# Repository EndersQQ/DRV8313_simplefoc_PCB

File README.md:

# DRV8313_simplefoc_PCB
A FOC driver board for controlling multiple BLDC motors using **SimpleFOC** and the **DRV8313** 3‑phase driver.

- Project: **FOC Motor Driver PCB**
- Driver IC: **Texas Instruments DRV8313**
- Firmware ecosystem: **Arduino and SimpleFOC library**

---

## Table of Contents
- [DRV8313_simplefoc_PCB](#drv8313_simplefoc_pcb)
  - [Overview](#overview)
  - [Features](#features)
  - [Repository Structure](#repository-structure)
  - [Hardware (PCB)](#hardware-pcb)
  - [Bill of Materials (BOM)](#bill-of-materials-bom)

---

## Overview
**DRV8313_simplefoc_PCB** is a compact motor driver board intended for **Field Oriented Control (FOC)** of BLDC motors. The board is designed to be used with a microcontroller running **SimpleFOC**, and provides the power stage based on the **DRV8313**.

> Goal: make it easy to build multi-motor setups by repeating the same driver channel design and keeping wiring/bring-up straightforward.

---

## Features
- DRV8313-based **3-phase BLDC** driver stage
- Designed for **SimpleFOC compatibility**
- Multi-motor oriented layout (repeatable channels)
- Test points / headers for bring-up (PWM, enable, faults, power) *(edit to match your PCB)*
- Power input + motor phase outputs *(edit to match your PCB)*

---

## Repository Structure
> Adjust folder names to match your repo.

- `Hardware/` – schematics, PCB layout, fabrication outputs (Gerbers)
- `BOM/` – BOM files, part numbers, assembly notes
- `Docs/` – wiring diagrams, photos, notes

---

## Hardware (PCB)
**Driver:** DRV8313 (3 half-bridges, BLDC driver)

### Key specs (fill these in)
- Supply voltage: **12 V**
- Max phase current (design target): **3 A**
- PWM input: **3 PWM**
- Control interface: **STM32**

### Photos / renders
Add images like this (put your images in `Docs/` or use GitHub uploads):

---

## Bill of Materials (BOM)
List critical parts (example layout below):

1. **DRV8313** – 3-phase driver IC
2. **ASC712** – Hall-effect current sensor
3. **LMR36015S** – synchronous step-down buck converter
4. **Connectors**
   - Power input (VIN/GND)
   - Motor outputs (U/V/W)
   - Control header (PWM/EN/GND/FAULT, etc.)
   - current sense output 

---

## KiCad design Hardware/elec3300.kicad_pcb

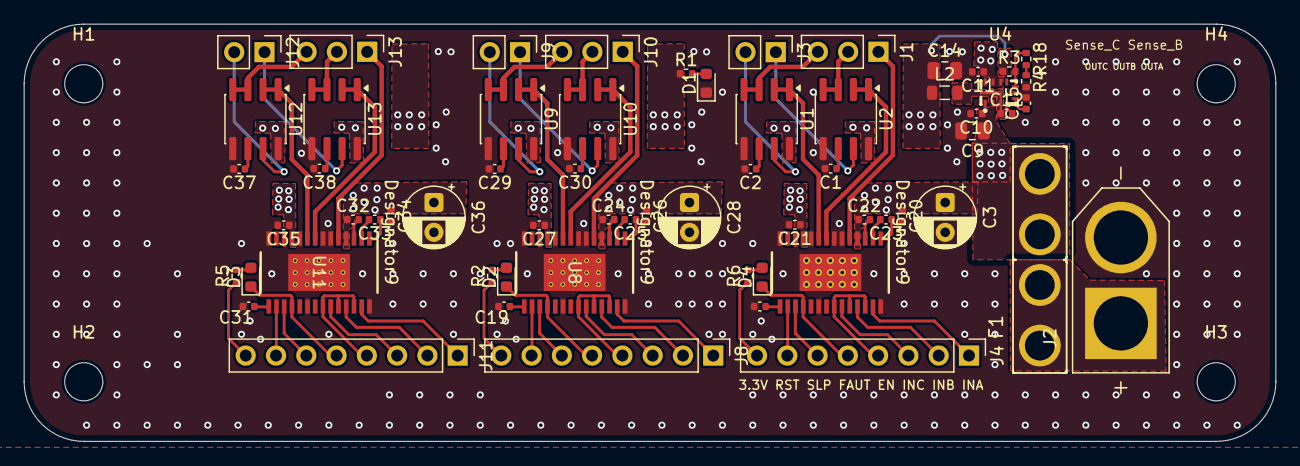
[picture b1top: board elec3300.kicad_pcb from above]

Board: 4 copper layers, 105.0 x 35.0 mm, 67 parts (0 on the bottom side), 74 nets.

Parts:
C1, C2, C29, C30, C37, C38: 1n; C_0402_1005Metric
C3, C28, C36: 100uF; CP_Radial_D5.0mm_P2.50mm
C8, C19, C31: 220n; C_0402_1005Metric
C9: 2.2u; C_0805_2012Metric
C10, C11: 22n; C_0402_1005Metric
C12, C20, C21, C22, C24, C26, C27, C32, C34, C35: 100n; C_0402_1005Metric
C14: 22u; C_0805_2012Metric
C15: 1u; C_0402_1005Metric
C23, C25, C33: 10n; C_0402_1005Metric
D1: LED; LED_0603_1608Metric
D2, D3, D4: LED; D_0603_1608Metric
F1: 01000057Z; FUSE_01000057Z
H1, H2, H3, H4: MountingHole; MountingHole_3.2mm_M3
J1, J10, J13: Conn_01x03; PinHeader_1x03_P2.54mm_Vertical
J2: XT60-M; AMASS_XT60-M
J3, J9, J12: Conn_01x02; PinHeader_1x02_P2.54mm_Vertical
J4, J8, J11: Conn_01x08; PinHeader_1x08_P2.54mm_Vertical
L2: 10u; L_0805_2012Metric
R1: 250; R_0402_1005Metric
R2, R5, R6: 1k5; R_0402_1005Metric
R3: 100k; R_0402_1005Metric
R4: 20k; R_0402_1005Metric
R18: 4.7k; R_0402_1005Metric
U1, U2, U9, U10, U12, U13: ACS712xLCTR-05B; SOIC-8_3.9x4.9mm_P1.27mm
U3, U8, U11: DRV8313PWP; PWP0028F_L
U4: LMR36015SFBRNXR; VQFN-12_L3.0-W2.0-P0.65-BL_TI_RNX

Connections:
+3.3V: J4.8, J8.8, J11.8, R2.1, R5.1, R6.1
+5V: C14.1, L2.1, R1.1, R3.1, U1.8 (VCC), U2.8 (VCC), U9.8 (VCC), U10.8 (VCC), U12.8 (VCC), U13.8 (VCC)
+12V: C3.1, C9.1, C10.1, C11.1, C20.1, C21.1, C22.1, C24.1, C26.1, C27.1, C28.1, C32.1, C34.1, C35.1, C36.1, F1.2A, F1.2B, U3.4 (VM), U3.11 (VM), U4.2 (VIN), U4.9 (EN), U4.10 (VIN), U8.4 (VM), U8.11 (VM), U11.4 (VM), U11.11 (VM)
/DRV8313_1/DRV_EN: J4.4, U3.22 (EN3), U3.24 (EN2), U3.26 (EN1)
/DRV8313_1/DRV_INA: J4.1, U3.27 (IN1)
/DRV8313_1/DRV_INB: J4.2, U3.25 (IN2)
/DRV8313_1/DRV_INC: J4.3, U3.23 (IN3)
/DRV8313_1/ISENSE_B: J3.1, U2.7 (VIOUT)
/DRV8313_1/ISENSE_C: J3.2, U1.7 (VIOUT)
/DRV8313_1/OUTA: J1.1, U3.5 (OUT1)
/DRV8313_1/OUTB: J1.2, U2.3 (IP-), U2.4 (IP-)
/DRV8313_1/OUTC: J1.3, U1.3 (IP-), U1.4 (IP-)
/DRV8313_1/PHB: U2.1 (IP+), U2.2 (IP+), U3.8 (OUT2)
/DRV8313_1/PHC: U1.1 (IP+), U1.2 (IP+), U3.9 (OUT3)
/DRV8313_1/~DRV_NFAULT: D4.1 (K), J4.5, U3.18 (~FAULT)
/DRV8313_1/~DRV_NRST: J4.7, U3.16 (~RESET)
/DRV8313_1/~DRV_NSLEEP: J4.6, U3.17 (~SLEEP)
/DRV8313_3/DRV_EN: J8.4, U8.22 (EN3), U8.24 (EN2), U8.26 (EN1)
/DRV8313_3/DRV_INA: J8.1, U8.27 (IN1)
/DRV8313_3/DRV_INB: J8.2, U8.25 (IN2)
/DRV8313_3/DRV_INC: J8.3, U8.23 (IN3)
/DRV8313_3/ISENSE_B: J9.1, U10.7 (VIOUT)
/DRV8313_3/ISENSE_C: J9.2, U9.7 (VIOUT)
/DRV8313_3/OUTA: J10.1, U8.5 (OUT1)
/DRV8313_3/OUTB: J10.2, U10.3 (IP-), U10.4 (IP-)
/DRV8313_3/OUTC: J10.3, U9.3 (IP-), U9.4 (IP-)
/DRV8313_3/PHB: U8.8 (OUT2), U10.1 (IP+), U10.2 (IP+)
/DRV8313_3/PHC: U8.9 (OUT3), U9.1 (IP+), U9.2 (IP+)
/DRV8313_3/~DRV_NFAULT: D2.1 (K), J8.5, U8.18 (~FAULT)
/DRV8313_3/~DRV_NRST: J8.7, U8.16 (~RESET)
/DRV8313_3/~DRV_NSLEEP: J8.6, U8.17 (~SLEEP)
/DRV8313_4/DRV_EN: J11.4, U11.22 (EN3), U11.24 (EN2), U11.26 (EN1)
/DRV8313_4/DRV_INA: J11.1, U11.27 (IN1)
/DRV8313_4/DRV_INB: J11.2, U11.25 (IN2)
/DRV8313_4/DRV_INC: J11.3, U11.23 (IN3)
/DRV8313_4/ISENSE_B: J12.1, U13.7 (VIOUT)
/DRV8313_4/ISENSE_C: J12.2, U12.7 (VIOUT)
/DRV8313_4/OUTA: J13.1, U11.5 (OUT1)
/DRV8313_4/OUTB: J13.2, U13.3 (IP-), U13.4 (IP-)
/DRV8313_4/OUTC: J13.3, U12.3 (IP-), U12.4 (IP-)
/DRV8313_4/PHB: U11.8 (OUT2), U13.1 (IP+), U13.2 (IP+)
/DRV8313_4/PHC: U11.9 (OUT3), U12.1 (IP+), U12.2 (IP+)
/DRV8313_4/~DRV_NFAULT: D3.1 (K), J11.5, U11.18 (~FAULT)
/DRV8313_4/~DRV_NRST: J11.7, U11.16 (~RESET)
/DRV8313_4/~DRV_NSLEEP: J11.6, U11.17 (~SLEEP)
GND: C1.2, C2.2, C3.2, C8.2, C9.2, C10.2, C11.2, C14.2, C15.2, C19.2, C20.2, C21.2, C26.2, C27.2, C28.2, C29.2, C30.2, C31.2, C34.2, C35.2, C36.2, C37.2, C38.2, D1.1 (K), J2.N (NEG), R4.2, U1.5 (GND), U2.5 (GND), U3.6 (PGND1), U3.7 (PGND2), U3.10 (PGND3), U3.14 (GND), U3.20 (GND), U3.28 (GND), U3.29 (EXP), U4.1 (PGND), U4.6 (AGND), U4.11 (PGND), U8.6 (PGND1), U8.7 (PGND2), U8.10 (PGND3), U8.14 (GND), U8.20 (GND), U8.28 (GND), U8.29 (EXP), U9.5 (GND), U10.5 (GND), U11.6 (PGND1), U11.7 (PGND2), U11.10 (PGND3), U11.14 (GND), U11.20 (GND), U11.28 (GND), U11.29 (EXP), U12.5 (GND), U13.5 (GND)
unnamed: D1.2 (A), R1.2
unnamed: D2.2 (A), R2.2
unnamed: D3.2 (A), R5.2
unnamed: D4.2 (A), R6.2
unnamed: R4.1, R18.2
unnamed: C2.1, U1.6 (FILTER)
unnamed: C1.1, U2.6 (FILTER)
unnamed: C23.2, U3.2 (CPH)
unnamed: C23.1, U3.1 (CPL)
unnamed: C8.1, U3.15 (V3P3)
unnamed: C22.2, U3.3 (VCP)
unnamed: C12.2, U4.4 (BOOT)
unnamed: R3.2, R18.1, U4.7 (FB)
unnamed: C12.1, L2.2, U4.3 (NC), U4.12 (SW)
unnamed: C15.1, U4.5 (VCC)
unnamed: C25.2, U8.2 (CPH)
unnamed: C25.1, U8.1 (CPL)
unnamed: C19.1, U8.15 (V3P3)
unnamed: C24.2, U8.3 (VCP)
unnamed: C29.1, U9.6 (FILTER)
unnamed: C30.1, U10.6 (FILTER)
unnamed: C33.2, U11.2 (CPH)
unnamed: C33.1, U11.1 (CPL)
unnamed: C31.1, U11.15 (V3P3)
unnamed: C32.2, U11.3 (VCP)
unnamed: C37.1, U12.6 (FILTER)
unnamed: C38.1, U13.6 (FILTER)
VCC: F1.1A, F1.1B, J2.P (POS)

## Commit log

2026-02-12 Enhance README with project details and structure
    Expanded the README to include detailed project information, features, repository structure, hardware specifications, and a bill of materials.
2026-02-12 Update README to remove installation section
    Removed 'Installation and Setup' section from the table of contents.
2026-02-12 Create new_1
2026-02-12 update PCB files
